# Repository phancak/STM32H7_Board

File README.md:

# STM32H7S3 High-Performance Modular Compute Platform

<div align="center">
  
  <br>
  <em>4-layer PCB diagram.</em>
</div>

## 📑 Quick Access
* [**📂 View Project Schematics (PDF)**](./Schematics/STM32H7_Board.pdf)
* [**📂 View PCB Layout (PDF)**](./PCB_Layout/STM32H7_Board.pdf)

## 📌 Project Overview
This project features a professional-grade, high-speed embedded system centered around the **STM32H7S3I8T6** (ARM Cortex-M7 running at 600 MHz). Developed as a post-graduate technical showcase, this board demonstrates proficiency in high-speed digital design, complex memory interfacing (SDRAM/NAND), and modular system architecture.

The platform is designed to serve as a high-bandwidth "Main Compute Module" that interfaces with expansion boards via a variety of industrial-standard protocols (PSSI, I2S, I2C, SPI, UART).

## 🛠 Technical Specifications

### Core Processing & Memory
* **MCU:** STM32H7S3I8T6 (600 MHz, 1MB SRAM, advanced security and graphics acceleration).
* **SDRAM:** 256 Mbit (IS42S83200J) @ 166 MHz — utilized for high-speed frame buffering and large-scale data processing.
* **NAND Flash:** 2 Gbit (MT29F2G08) — providing robust, non-volatile storage for OS and data logging.

### Connectivity & Expansion
* **PSSI (Parallel Synchronous Slave Interface):** Dedicated high-speed parallel bus for camera or FPGA data acquisition.
* **Audio (I2S):** High-fidelity audio interface with dedicated Master Clock (MCK) routing.
* **USB-C OTG:** High-speed (480 Mbps) data support with integrated UCPD (USB-C Power Delivery) logic.
* **Peripheral Bus:** Fully broken-out I2C, SPI, and UART headers for modular hardware stacking.

## 🚀 Engineering Design Highlights

### 1. High-Speed Signal Integrity (SI)
* **4-Layer Stackup:** Designed with a dedicated Ground plane (L2) and Power plane (L3) to provide a stable reference and minimize return path inductance.
* **Impedance Control:** Managed 90Ω differential pairs for USB High-Speed and 50Ω single-ended traces for memory clocks.
* **Memory Routing:** Implemented length-matching and fly-by/star topology considerations for the SDRAM address and data bus to meet strict setup and hold time requirements at 166 MHz.

### 2. Power Delivery Network (PDN)
* **Core Stability:** Designed for the 600 MHz switching transients of the Cortex-M7 using low-ESR ceramic decoupling arrays.
* **Via Stitching:** Utilized parallel via strategies (e.g., dual 0.3mm vias) for high-current power paths to minimize IR drop and parasitic inductance.

### 3. Hardware Robustness
* **ESD Protection:** Integrated low-capacitance TVS diode arrays on USB-C lines to protect sensitive MCU transceivers.
* **Signal Conditioning:** Series termination resistors on high-speed clocks (MCK, CK) and proper pull-up configurations for Open-Drain lines (NAND_RB).

## 🔬 Testing & Validation Plan

To ensure the reliability of a 600 MHz system, the following hardware validation protocols were implemented:

### 1. Signal Integrity (SI) Verification
Using a high-bandwidth digital oscilloscope (2 GHz+), the following critical signals are probed to verify timing margins and signal quality:
* **SDRAM Clock (166 MHz):** Measured for overshoot, undershoot, and rise/fall times ($t_R/t_F$) to ensure compliance with the IS42S83200J datasheet. 
* **Eye Diagram Analysis:** Performed on the USB High-Speed (480 Mbps) differential pairs to validate the $90\Omega$ impedance matching and ensure zero bit errors.
* **Clock Jitter:** Measured the stability of the I2S Master Clock (MCK) to prevent phase noise in audio reconstruction.

### 2. Power Integrity (PI) & Thermal Analysis
* **DC Load Testing:** Verified the 3.3V and 1.1V rails under maximum CPU/SDRAM load to ensure the IR drop across the power plane remains within $\pm 3\%$.
* **Transient Response:** Observed the $V_{CORE}$ rail during high-frequency switching to validate the effectiveness of the decoupling capacitor network.
* **Thermal Imaging:** Monitored the STM32H7S3 and SDRAM during continuous burst transfers to identify potential hotspots on the 4-layer stackup.

### 3. Memory Interface Stress Testing
* **MemTest86-style Routines:** Implemented custom firmware to perform pseudo-random pattern writes/reads across the entire 256 Mbit SDRAM space to check for bit-flip errors caused by crosstalk or timing skew.
* **NAND Bad Block Management:** Validated the ECC (Error Correction Code) and wear-leveling logic within the MT29F2G08 driver.

## 🛠 Skills Demonstrated
* **Hardware:** High-speed PCB design (Altium/KiCad), Differential Pair Routing, PDN Optimization, ESD/EMI protection.
* **Firmware:** C/C++, STM32 CubeHAL, Memory Management Units (MMU), DMA configuration.
* **Tools:** Digital Oscilloscopes, Logic Analyzers, Spectrum Analyzers.

## 📂 Repository Structure
* `/Hardware`: Schematic (PDF/Source), PCB Layout, and Layer Stackup definitions.
* `/Firmware`: BSP (Board Support Package), memory initialization code, and driver implementations.
* `/Docs`: Power budget analysis and timing margin calculations.

## 🎓 About the Author
I am a recent **Electrical Engineering graduate from the University of British Columbia (UBC)**. This project represents my ability to transition theoretical academic knowledge into a complex, manufacturable high-speed digital system.

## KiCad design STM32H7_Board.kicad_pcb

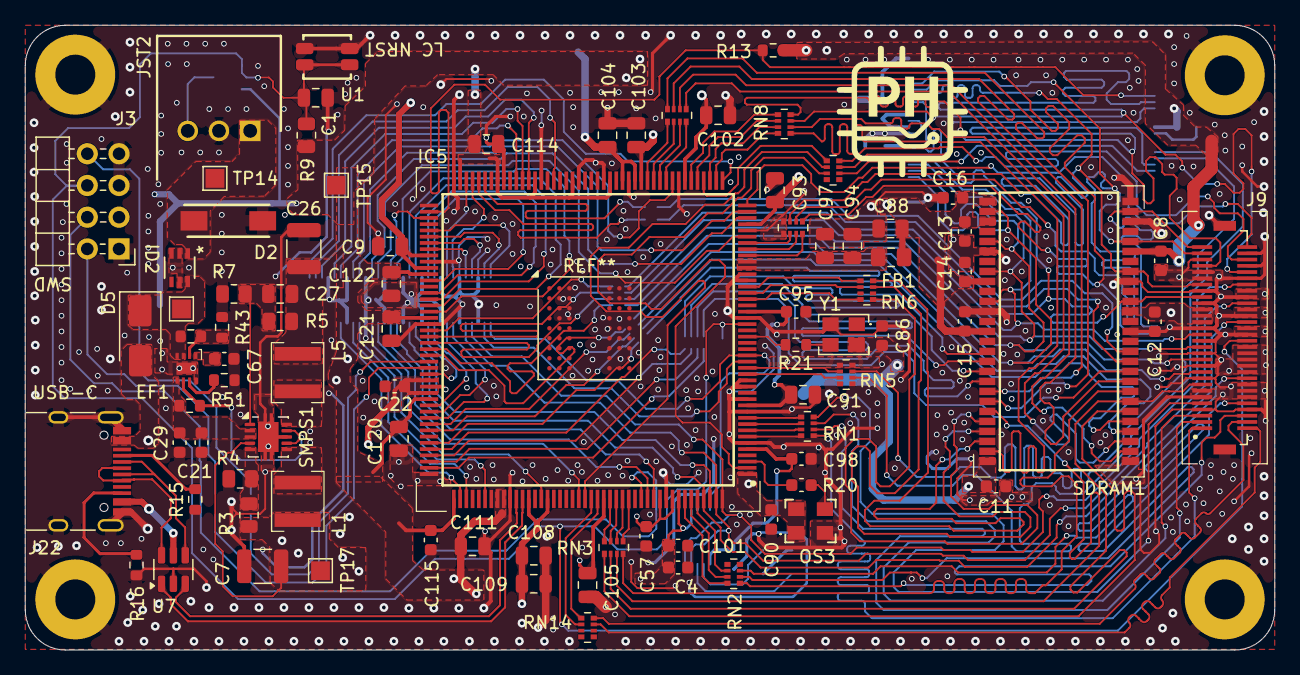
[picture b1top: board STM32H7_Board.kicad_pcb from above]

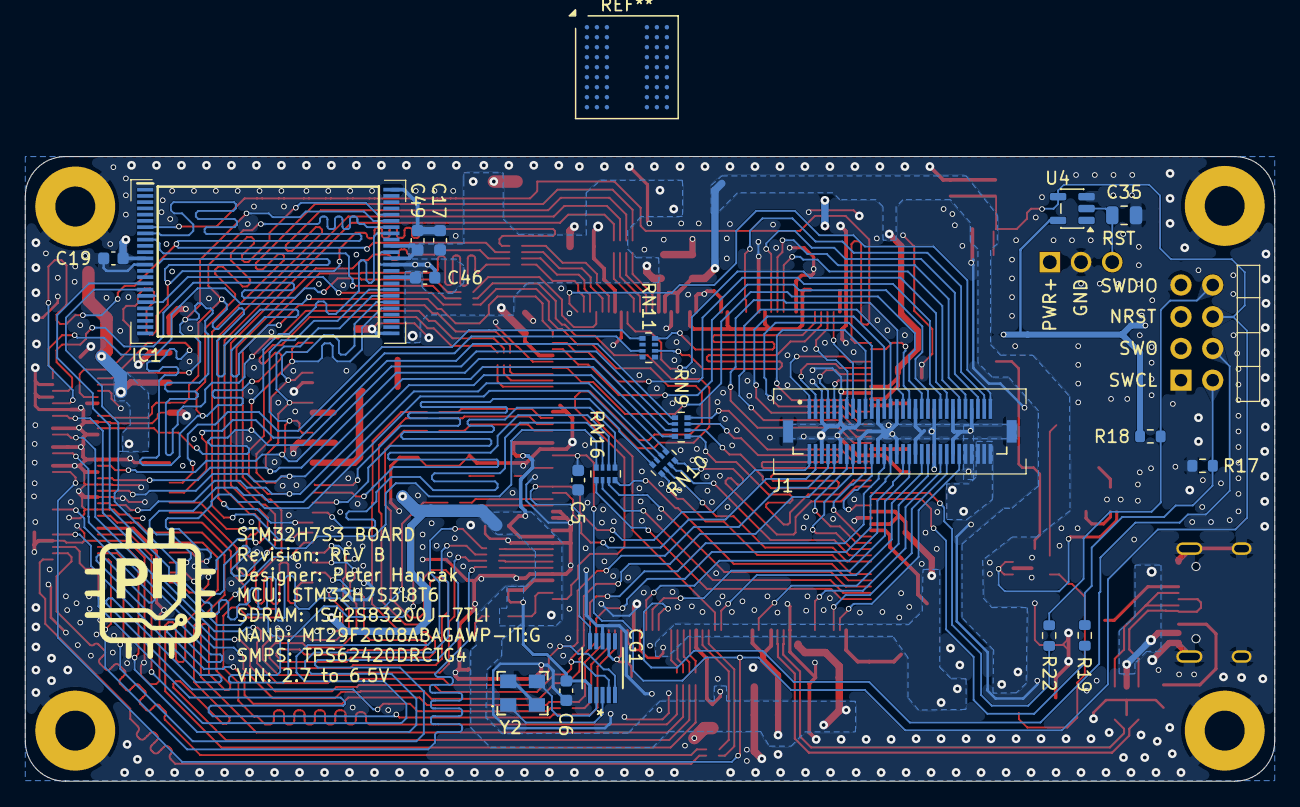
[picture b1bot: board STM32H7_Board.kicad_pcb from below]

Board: 4 copper layers, 100.0 x 50.0 mm, 110 parts (20 on the bottom side), 167 nets.

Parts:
C1: 1uF; C_0805_2012Metric
C4, C5, C6, C8, C11, C12, C13, C14, C15, C16, C17, C19, C46, C49, C95, C98, C101, C115: 100n; C_0603_1608Metric
C7, C26: 22u; C_1210_3225Metric
C9, C88, C104: 4u7; C_0805_2012Metric
C21, C29: 10u; C_0603_1608Metric
C22, C57: 4u7; C_0603_1608Metric
C27: 33p; C_0805_2012Metric
C35, C91, C93, C97, C102, C103, C105, C108, C109, C114, C120, C121, C122: 100n; C_0805_2012Metric
C67: 3n3; C_0603_1608Metric
C86, C90: 10n; C_0603_1608Metric
C94, C111: 1u; C_0805_2012Metric
CG1: Clock_Gen_SI5351A-B-GT; Clock_Gen_SI5351
D2: SMAJ6.0A; DO-214AC-2
D5: SS34-E3/57T; D_SMA
EF1: EFUSE_TPS259531DSGR; EF_TPS259531DSGR
FB1: BLM21PG601SN1D_0805; C_0805_2012Metric_Pad1.18x1.45mm_HandSolder
H1, H2, H3, H4: MountingHole_Pad; MountingHole_3.2mm_M3_Pad
IC1: NAND_MX30LF1G18AC-TI; NAND_MT29F1G08ABAEAWP-IT_E_TR_SOP50P2000X120-48N
IC5: STM32H7S3I8T6 LQFP 176; QFP50P2600X2600X160-176N
ID2: ID_LM66100DCKR
J1, J9: BTB_10132798-062100LF; BTB_AMPHENOL_10132798-062100LF
J3: SWDB; PinHeader_2x04_P2.54mm_Horizontal
J22: USB_C_Receptacle_USB2.0_16P; USB_C_Receptacle_HRO_TYPE-C-31-M-12
JST2: JST_S3B-XH-2.54; JST_S3B-XH-SHDRRA3W64P0X250_1X3_990X1150X610P
L1: 2u2 NR4020S2R2MT; L_NR4020S2R2MT
L5: 3u3 CPN4020H3R3MT; L_NR4020S2R2MT
OS3: Oscillator_ECS-327MVATX-3-CN-TR; Oscillator_ECS327MVATX3CNTR
R3, R4, R7: 180k; R_0805_2012Metric
R5: 806k; R_0805_2012Metric
R9: 10k; R_0805_2012Metric_1
R13: 4k7; R_0603_1608Metric
R15, R16: 5k1; R_0603_1608Metric
R17, R18: 10k; R_0603_1608Metric
R19, R22: 22R; R_0603_1608Metric
R20: 22R; C_0603_1608Metric
R21: 51R; R_0603_1608Metric
R38, R52: 1M; R_0603_1608Metric
R43: 383k; R_0603_1608Metric
R51: 487R; R_0603_1608Metric
RN1, RN2, RN3, RN4, RN5, RN6, RN7, RN8, RN9, RN10, RN11, RN13, RN14, RN16: 33R; R_Array_Convex_4x0402
SDRAM1: SDRAM_AS4C32M8SA-7TCN; SDRAM_IS42S16320F-6TL
SMPS1: SMPS_TPS62420DRCTG4; VSON-10-1EP_3x3mm_P0.5mm_EP1.65x2.4mm
TP13, TP14, TP15, TP17: TestPoint; TestPoint_Pad_1.5x1.5mm
U1: Button_SKSCLCE010
U4: SN74LVC1G07DBVR; SOT-23-5
U7: USBLC6-2SC6; SOT-23-6
Y1: ECS-3225SMVQ-240-DS-TR; Oscillator_ASE50000MHZLRT
Y2: TSX-3225 26.0000MF09Z-AC0; Oscillator_ECS327MVATX3CNTR

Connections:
/FMC_A0: RN6.1 (R1.1), SDRAM1.23 (A0)
/FMC_A1: RN6.3 (R3.1), SDRAM1.24 (A1)
/FMC_A2: RN6.4 (R4.1), SDRAM1.25 (A2)
/FMC_A3: RN8.1 (R1.1), SDRAM1.26 (A3)
/FMC_A4: RN4.1 (R1.1), SDRAM1.29 (A4)
/FMC_A5: RN8.2 (R2.1), SDRAM1.30 (A5)
/FMC_A6: RN10.6 (R3.2), SDRAM1.31 (A6)
/FMC_A7: RN10.7 (R2.2), SDRAM1.32 (A7)
/FMC_A8: RN3.5 (R4.2), SDRAM1.33 (A8)
/FMC_A9: J9.8, RN3.6 (R3.2), SDRAM1.34 (A9)
/FMC_A10: RN3.7 (R2.2), SDRAM1.22 (A10)
/FMC_A11: RN3.8 (R1.2), SDRAM1.35 (A11)
/FMC_A12: RN4.2 (R2.1), SDRAM1.36 (A12)
/FMC_D0: IC1.29 (I/O0), J9.10, RN10.5 (R4.2), SDRAM1.2 (DQ0)
/FMC_D1: IC1.30 (I/O1), J9.12, RN9.8 (R1.2), SDRAM1.5 (DQ1)
/FMC_D2: IC1.31 (I/O2), J9.14, RN9.7 (R2.2), SDRAM1.8 (DQ2)
/FMC_D3: IC1.32 (I/O3), J9.16, RN9.6 (R3.2), SDRAM1.11 (DQ3)
/FMC_D4: IC1.41 (I/O4), J9.22, RN9.5 (R4.2), SDRAM1.44 (DQ4)
/FMC_D5: IC1.42 (I/O5), J9.24, RN7.3 (R3.1), SDRAM1.47 (DQ5)
/FMC_D6: IC1.43 (I/O6), J9.29, RN7.2 (R2.1), SDRAM1.50 (DQ6)
/FMC_D7: IC1.44 (I/O7), J9.30, RN7.1 (R1.1), SDRAM1.53 (DQ7)
/FMC_D8: J9.59, RN14.8 (R1.2)
/FMC_D9: J9.58, RN2.5 (R4.2)
/FMC_D10: J9.56, RN2.6 (R3.2)
/FMC_D11: J9.52, RN2.7 (R2.2)
/FMC_D12: J9.1, RN1.1 (R1.1)
/FMC_D13: J9.2, RN1.2 (R2.1)
/FMC_D14: J9.3, RN1.3 (R3.1)
/FMC_D15: J9.5, RN1.4 (R4.1)
/Interface_Headers/BTB1: IC5.93 (PB12), J1.1
/Interface_Headers/BTB2: IC5.94 (PB13), J1.2
/Interface_Headers/BTB4: IC5.95 (PB14), J1.4
/Interface_Headers/BTB5: IC5.96 (PB15), J1.5
/Interface_Headers/BTB7: IC5.85 (PD10), J1.7
/Interface_Headers/BTB8: IC5.86 (PD11), J1.8
/Interface_Headers/BTB10: IC5.101 (PD14), J1.10
/Interface_Headers/BTB11: IC5.103 (PC6), J1.11
/Interface_Headers/BTB13: IC5.104 (PC7), J1.13
/Interface_Headers/BTB14: IC5.105 (PC8), J1.14
/Interface_Headers/BTB16: IC5.106 (PC9), J1.16
/Interface_Headers/BTB17: IC5.91 (PB10), J1.17
/Interface_Headers/BTB19: IC5.39 (PA3), J1.19
/Interface_Headers/BTB20: IC5.42 (PA4), J1.20
/Interface_Headers/BTB22: IC5.43 (PA5), J1.22
/Interface_Headers/BTB23: IC5.53 (PF11), J1.23
/Interface_Headers/BTB25: IC5.78 (PP7), J1.25
/Interface_Headers/BTB26: IC5.77 (PO2), J1.26
/Interface_Headers/BTB28: IC5.76 (PP6), J1.28
/Interface_Headers/BTB29: IC5.72 (PP5), J1.29
/Interface_Headers/BTB30: IC5.45 (PA7), J1.30
/Interface_Headers/BTB31: CG1.10 (CLK0), IC5.20 (PF8), J1.60
/Interface_Headers/BTB32: IC5.19 (PF7), J1.59
/Interface_Headers/BTB34: CG1.5 (SDA), IC5.176 (PB9), J1.57, J9.37
/Interface_Headers/BTB35: CG1.4 (SCL), IC5.175 (PB8), J1.56, J9.40
/Interface_Headers/BTB37: IC5.122 (PC11), J1.54
/Interface_Headers/BTB38: IC5.123 (PC12), J1.53
/Interface_Headers/BTB40: IC5.121 (PC10), J1.51
/Interface_Headers/BTB41: IC5.116 (PA15), J1.50
/Interface_Headers/BTB43: IC5.174 (PB7), J1.48
/Interface_Headers/BTB44: IC5.173 (PB6), J1.47, J9.43
/Interface_Headers/BTB46: IC5.165 (PB5), J1.45
/Interface_Headers/BTB47: IC5.164 (PB4), J1.44
/Interface_Headers/BTB49: IC5.153 (BOOT0), J1.42
/Interface_Headers/BTB50: IC5.147 (PM9), J1.41
/Interface_Headers/BTB52: IC5.138 (PM2), J1.39
/Interface_Headers/BTB53: IC5.135 (PD4), J1.38
/Interface_Headers/BTB55: IC5.134 (PD3), J1.36
/Interface_Headers/NRST: C1.2, C5.2, IC5.25 (NRST), J3.6, J9.46, R9.1, U1.3, U1.4, U4.4
/Interface_Headers/SWCLK: IC5.115 (PA14), R19.2
/Interface_Headers/SWCLK_R: J3.2, R17.2, R19.1
/Interface_Headers/SWDIO: IC5.114 (PA13), R22.2
/Interface_Headers/SWDIO_R: J3.8, R18.2, R22.1
/Interface_Headers/SWO: IC5.163 (PB3), J3.4
/Interface_Headers/USB_D2+: J22.A6 (D+), J22.B6 (D+), U7.6 (I/O1)
/Interface_Headers/USB_D2-: J22.A7 (D-), J22.B7 (D-), U7.4 (I/O2)
/Interface_Headers/USB_DI_D2+: IC5.144 (PM6), U7.1 (I/O1)
/Interface_Headers/USB_DI_D2-: IC5.143 (PM5), U7.3 (I/O2)
/LCD_Interface/FMC_NE3: J9.60, RN14.7 (R2.2)
/LCD_Interface/FMC_NOE: IC1.8 (RE#), J9.35, RN8.3 (R3.1)
/LCD_Interface/FMC_NWE: IC1.18 (WE#), J9.27, RN8.4 (R4.1)
/LCD_Interface/LCD_TE: J9.33, RN13.8 (R1.2)
/LCD_Interface/LED_Driver_CTRL: IC5.44 (PA6), J9.31
/Memory/NAND_ALE: IC1.17 (ALE), RN5.3 (R3.1)
/Memory/NAND_CE#: IC1.9 (CE#), RN13.7 (R2.2)
/Memory/NAND_CLE: IC1.16 (CLE), RN5.2 (R2.1)
/Memory/NAND_R/B#: IC1.7 (R/B#), IC5.90 (PD13), R13.2
/Memory/NAND_WP#: IC1.19 (WP#), RN13.6 (R3.2)
/Memory/SDRAM_BA0: RN4.3 (R3.1), SDRAM1.20 (BA0)
/Memory/SDRAM_BA1: RN4.4 (R4.1), SDRAM1.21 (BA1)
/Memory/SDRAM_CKE: RN16.8 (R1.2), SDRAM1.37 (CKE)
/Memory/SDRAM_CLK: RN11.3 (R3.1), SDRAM1.38 (CLK)
/Memory/SDRAM_DQMH: RN11.1 (R1.1), SDRAM1.39 (DQMH)
/Memory/SDRAM_~CAS: RN16.6 (R3.2), SDRAM1.17 (~CAS)
/Memory/SDRAM_~CS: RN16.7 (R2.2), SDRAM1.19 (~CS)
/Memory/SDRAM_~RAS: RN16.5 (R4.2), SDRAM1.18 (~RAS)
/Memory/SDRAM_~WE: RN10.8 (R1.2), SDRAM1.16 (~WE)
/Power_Management/ADJ2: C27.1, R5.2, R7.1, SMPS1.1 (ADJ2)
/Power_Management/DEF_1: R3.2, R4.1, SMPS1.5 (DEF_1)
/Power_Management/DVDT_1: C67.2, EF1.1 (DVDT)
/Power_Management/EN/UVLO_1: EF1.2 (EN/UVLO), R38.2, R43.1
/Power_Management/PWR+: D2.1 (K), ID2.1 (VIN), JST2.1 (PWR+), TP14.1 (1_1)
/Power_Management/PWR+_EF: C21.1, C29.1, EF1.5 (OUT), R52.1, SMPS1.2 (MODE_DATA), SMPS1.3 (VIN)
/Power_Management/PWR+_PP: D5.1 (K), EF1.3 (IN), EF1.4 (IN__1), ID2.6 (VOUT), R38.1, TP13.1 (1_1)
/Power_Management/RST_PWR: C35.1, JST2.3 (RST), U4.2
/Power_Management/SW1: L1.1, SMPS1.6 (SW1)
/Power_Management/SW2: L5.1, SMPS1.10 (SW2)
/Power_Management/~FLT: EF1.6 (~FLT), R52.2, SMPS1.7 (EN1), SMPS1.9 (EN2)
/STM32H7S3I8T6/FMC_A0_R: IC5.29 (PC1), RN6.8 (R1.2)
/STM32H7S3I8T6/FMC_A1_R: IC5.30 (PC2), RN6.6 (R3.2)
/STM32H7S3I8T6/FMC_A2_R: IC5.31 (PC3), RN6.5 (R4.2)
/STM32H7S3I8T6/FMC_A3_R: IC5.46 (PC4), RN8.8 (R1.2)
/STM32H7S3I8T6/FMC_A4_R: IC5.54 (PE7), RN4.8 (R1.2)
/STM32H7S3I8T6/FMC_A5_R: IC5.47 (PC5), RN8.7 (R2.2)
/STM32H7S3I8T6/FMC_A6_R: IC5.124 (PD0), RN10.3 (R3.1)
/STM32H7S3I8T6/FMC_A7_R: IC5.125 (PD1), RN10.2 (R2.1)
/STM32H7S3I8T6/FMC_A8_R: IC5.158 (PF0), RN3.4 (R4.1)
/STM32H7S3I8T6/FMC_A9_R: IC5.159 (PF1), RN3.3 (R3.1)
/STM32H7S3I8T6/FMC_A10_R: IC5.160 (PF2), RN3.2 (R2.1)
/STM32H7S3I8T6/FMC_A11_R: IC5.161 (PF3), RN3.1 (R1.1)
/STM32H7S3I8T6/FMC_A12_R: IC5.55 (PE8), RN4.7 (R2.2)
/STM32H7S3I8T6/FMC_ALE_R: IC5.18 (PF6), RN5.6 (R3.2)
/STM32H7S3I8T6/FMC_BA0_R: IC5.56 (PE9), RN4.6 (R3.2)
/STM32H7S3I8T6/FMC_BA1_R: IC5.57 (PE10), RN4.5 (R4.2)
/STM32H7S3I8T6/FMC_CLE_R: IC5.17 (PF5), RN5.7 (R2.2)
/STM32H7S3I8T6/FMC_D0_R: IC5.113 (PA12), RN10.4 (R4.1)
/STM32H7S3I8T6/FMC_D1_R: IC5.112 (PA11), RN9.1 (R1.1)
/STM32H7S3I8T6/FMC_D2_R: IC5.111 (PA10), RN9.2 (R2.1)
/STM32H7S3I8T6/FMC_D3_R: IC5.110 (PA9), RN9.3 (R3.1)
/STM32H7S3I8T6/FMC_D4_R: IC5.109 (PA8), RN9.4 (R4.1)
/STM32H7S3I8T6/FMC_D5_R: IC5.38 (PA2), RN7.6 (R3.2)
/STM32H7S3I8T6/FMC_D6_R: IC5.37 (PA1), RN7.7 (R2.2)
/STM32H7S3I8T6/FMC_D7_R: IC5.36 (PA0), RN7.8 (R1.2)
/STM32H7S3I8T6/FMC_D8_R: IC5.156 (PD7), RN14.1 (R1.1)
/STM32H7S3I8T6/FMC_D9_R: IC5.170 (PE0), RN2.4 (R4.1)
/STM32H7S3I8T6/FMC_D10_R: IC5.171 (PE1), RN2.3 (R3.1)
/STM32H7S3I8T6/FMC_D11_R: IC5.172 (PE2), RN2.2 (R2.1)
/STM32H7S3I8T6/FMC_D12_R: IC5.7 (PE3), RN1.8 (R1.2)
/STM32H7S3I8T6/FMC_D13_R: IC5.8 (PE4), RN1.7 (R2.2)
/STM32H7S3I8T6/FMC_D14_R: IC5.9 (PE5), RN1.6 (R3.2)
/STM32H7S3I8T6/FMC_D15_R: IC5.10 (PE6), RN1.5 (R4.2)
/STM32H7S3I8T6/FMC_NCE_R: IC5.154 (PD5), RN13.2 (R2.1)
/STM32H7S3I8T6/FMC_NOE_R: IC5.49 (PB1), RN8.6 (R3.2)
/STM32H7S3I8T6/FMC_NWE_R: IC5.50 (PB2), RN8.5 (R4.2)
/STM32H7S3I8T6/PB0_GFXTIM_TE_R: IC5.48 (PB0), RN13.1 (R1.1)
/STM32H7S3I8T6/PC13_R: IC5.2 (PC13), RN13.3 (R3.1)
/STM32H7S3I8T6/PC14-OSC32_IN: IC5.3 (PC14-OSC32_IN), R20.2
/STM32H7S3I8T6/PD6_FMC_NE3_R: IC5.155 (PD6), RN14.2 (R2.1)
/STM32H7S3I8T6/PD8_FMC_NBL0_R: IC5.83 (PD8), RN11.8 (R1.2)
/STM32H7S3I8T6/PD9_FMC_SDCLK_R: IC5.84 (PD9), RN11.6 (R3.2)
/STM32H7S3I8T6/PE11_FMC_SDNWE_R: IC5.127 (PE11), RN10.1 (R1.1)
/STM32H7S3I8T6/PE12_FMC_SDNRAS_R: IC5.128 (PE12), RN16.4 (R4.1)
/STM32H7S3I8T6/PE13_FMC_SDNCAS_R: IC5.129 (PE13), RN16.3 (R3.1)
/STM32H7S3I8T6/PE14_FMC_SDNE0_R: IC5.130 (PE14), RN16.2 (R2.1)
/STM32H7S3I8T6/PE15_FMC_SDCKE0_R: IC5.131 (PE15), RN16.1 (R1.1)
/STM32H7S3I8T6/PH0-OSC_IN: IC5.23 (PH0-OSC_IN), R21.2
/STM32H7S3I8T6/VDDA_FB: C94.1, C97.1, FB1.2, IC5.34 (VREFP), IC5.35 (VDDA)
GND: C1.1, C4.1, C5.1, C6.1, C7.1, C8.2, C9.2, C11.2, C12.2, C13.2, C14.2, C15.2, C16.2, C17.2, C19.2, C21.2, C22.2, C26.1, C29.2, C35.2, C46.2, C49.2, C57.2, C67.1, C86.2, C88.2, C90.1, C91.2, C93.2, C94.2, C95.2, C97.2, C98.2, C101.2, C102.2, C103.2, C104.2, C105.2, C108.2, C109.1, C111.1, C114.2, C115.2, C120.2, C121.2, C122.2, CG1.8 (GND), D2.2 (A), EF1.8 (GND), EF1.9 (GND__1), H1.1 (1_1), H2.1 (1_1), H3.1 (1_1), H4.1 (1_1), IC1.13 (VSS_1), IC1.25 (VSS_2), IC1.36 (VSS_3), IC1.38 (PT), IC1.48 (VSS_4), IC5.6 (VSS_1), IC5.11 (VSS_2), IC5.13 (VSSSMPS), IC5.15 (VDDSMPS), IC5.16 (VFBSMPS), IC5.26 (VSS_3), IC5.32 (VSSA), IC5.33 (VREFM), IC5.40 (VSS_4), IC5.52 (VSS_5), IC5.60 (VSS_6), IC5.64 (VSS_7), IC5.68 (VSS_8), IC5.74 (VSS_9), IC5.80 (VSS_10), IC5.88 (VSS_11), IC5.98 (VSS_12), IC5.108 (VSS_13), IC5.118 (VSS_14), IC5.132 (VSS_15), IC5.142 (VSSUSB), IC5.167 (VSS_16), ID2.2 (GND), ID2.3 (*CE), ID2.5 (ST), J1.3, J1.6, J1.9, J1.12, J1.15, J1.18, J1.21, J1.24, J1.27, J1.34, J1.35, J1.37, J1.40, J1.43, J1.46, J1.49, J1.52, J1.55, J1.58, J1.SH1, J1.SH2, J3.1, J3.5, J3.7, J9.4, J9.6, J9.7, J9.9, J9.11, J9.13, J9.15, J9.17, J9.21, J9.23, J9.25, J9.26, J9.28, J9.32, J9.34, J9.36, J9.38, J9.39, J9.41, J9.42, J9.44, J9.45, J9.47, J9.48, J9.49, J9.50, J9.51, J9.53, J9.54, J9.55, J9.57, J9.SH1, J9.SH2, J22.A1 (GND), J22.A12 (GND), J22.B1 (GND), J22.B12 (GND), J22.S1 (SHIELD), JST2.2 (PWR-), OS3.2 (GND), R4.2, R7.2, R15.2, R16.2, R17.1, R43.2, R51.2, RN5.4 (R4.1), RN5.5 (R4.2), RN7.4 (R4.1), RN7.5 (R4.2), SDRAM1.6 (VSSQ_1), SDRAM1.12 (VSSQ_2), SDRAM1.28 (VSS_1), SDRAM1.41 (VSS_2), SDRAM1.46 (VSSQ_3), SDRAM1.52 (VSSQ_4), SDRAM1.54 (VSS_3), SMPS1.8 (GND), SMPS1.11 (PAD), U1.1, U1.2, U4.3 (GND), U7.2 (GND), Y1.2 (GND/CASE), Y2.2, Y2.4
unnamed: CG1.2 (XA), Y2.3
unnamed: CG1.3 (XB), Y2.1
unnamed: EF1.7 (ILM), R51.1
unnamed: J22.A5 (CC1), R15.1
unnamed: J22.B5 (CC2), R16.1
unnamed: OS3.3 (OUTPUT), R20.1
unnamed: R21.1, Y1.3 (OUTPUT)
SMPS_OUT1_1V2+: C7.2, C9.1, C22.1, C57.1, C104.1, IC5.59 (VDDLDO_1), IC5.61 (VCAP1), IC5.97 (VCAP2), IC5.99 (VDDLDO_2), IC5.117 (VCAP3), IC5.119 (VDDLDO_3), IC5.166 (VCAP4), IC5.168 (VDDLDO_4), L1.2, R3.1, SMPS1.4 (FB1), TP17.1 (1_1)
SMPS_OUT2_3V3+: C4.2, C6.2, C8.1, C11.1, C12.1, C13.1, C14.1, C15.1, C16.1, C17.1, C19.1, C26.2, C27.2, C46.1, C49.1, C86.1, C88.1, C90.2, C91.1, C93.1, C95.1, C98.1, C101.1, C102.1, C103.1, C105.1, C108.1, C109.2, C111.2, C114.1, C115.1, C120.1, C121.1, C122.1, CG1.1 (VDD), CG1.7 (VDDO), FB1.1, IC1.12 (VCC_1), IC1.34 (VCC_2), IC1.37 (VCC_3), IC1.39 (VCC_4), IC5.1 (VBAT), IC5.5 (VDD_1), IC5.12 (VDD_2), IC5.27 (VDD_3), IC5.41 (VDD_4), IC5.51 (VDD_5), IC5.58 (VDD_6), IC5.63 (VDDXSPI1_1), IC5.69 (VDDXSPI1_2), IC5.75 (VDDXSPI1_3), IC5.81 (VDDXSPI1_4), IC5.87 (VDD_7), IC5.100 (VDD_8), IC5.107 (VDD_9), IC5.120 (VDD_10), IC5.133 (VDD_11), IC5.140 (VDD50USB), IC5.141 (VDD33USB), IC5.145 (DVDD), IC5.148 (VDD_12), IC5.157 (VDD_13), IC5.169 (VDD_14), J1.31, J1.32, J1.33, J3.3, J9.18, J9.19, J9.20, L5.2, OS3.1 (TRI-STATE), OS3.4 (VDD), R5.1, R9.2, R13.1, R18.1, SDRAM1.1 (VDD_1), SDRAM1.3 (VDDQ_1), SDRAM1.9 (VDDQ_2), SDRAM1.14 (VDD_2), SDRAM1.27 (VDD_3), SDRAM1.43 (VDDQ_3), SDRAM1.49 (VDDQ_4), TP15.1 (1_1), U4.5 (VCC), Y1.4 (VDD)
USB_VBUS+: D5.2 (A), J22.A4 (VBUS), J22.A9 (VBUS), J22.B4 (VBUS), J22.B9 (VBUS), U7.5 (VBUS)

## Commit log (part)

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2026-03-17 Pin typo fix
2026-03-17 Update Readme file
2026-03-25 Added I2C to the LCD interface
2026-03-25 General PCB tweaks
2026-05-13 NAND Interface
